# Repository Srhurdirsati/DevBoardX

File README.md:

# DevBoard X
Yo Boizzz , This Is A MACROPAD (not really , it has 20 keys) Named DevBoard X That Includes 20 Keys [Mechanical] with 4x EC11 Rotary Encoders And 1x OLED Diplay...

# FEATURES 
1->> Full Of Functionable Keys { 20 ,MORE THAN ENOUGH }</n>

2->> Rotary Encoders { Cool Scrolllss }</n>

3->> Fully Customizable { Modify The Code For Ur Own Functioning }</n>

# IMAGESSS

# 📋 Bill of Materials (BOM)

| Component | Quantity | Specification | Unit Price | Total Price |
|-----------|----------|---------------|------------|-------------|
| **Microcontroller** | 1 | Raspberry Pi Pico | $4.88 | $4.88 |
| **Rotary Encoders** | 4 | EC11 (Vertical, 20mm shaft) | 0.87 | 3.48 |
| **Keyswitches** | 20 | Outemu Red Cherry MX  | 1.51 | $20 |
| **Diodes** | 20 | 1N4148 (THT) | $0.3 | $2.32 |
| **PCB** | 5 | Custom macropad (5x4 matrix) | $25 with shipping | $25 with shipping |
| **Case & Knobs** | 1 | 3D Printed | Done By Printing Legion | Done By Printing Legion |
| **USB Cable** | 1 | Micro-USB or USB-C | $3.32 | $2.32 |

## JLCPCB

**IDK WHY EVERYTHING IS SO EXPENSIVE IN INDIA**

**Total Estimated Cost**: `$72-75 WITH SHIPPING CHARGES INCLUDED`
**I Tried My best To Decrease The cost As Much As Possible , Would Be Much Cheaper If I Was In US**

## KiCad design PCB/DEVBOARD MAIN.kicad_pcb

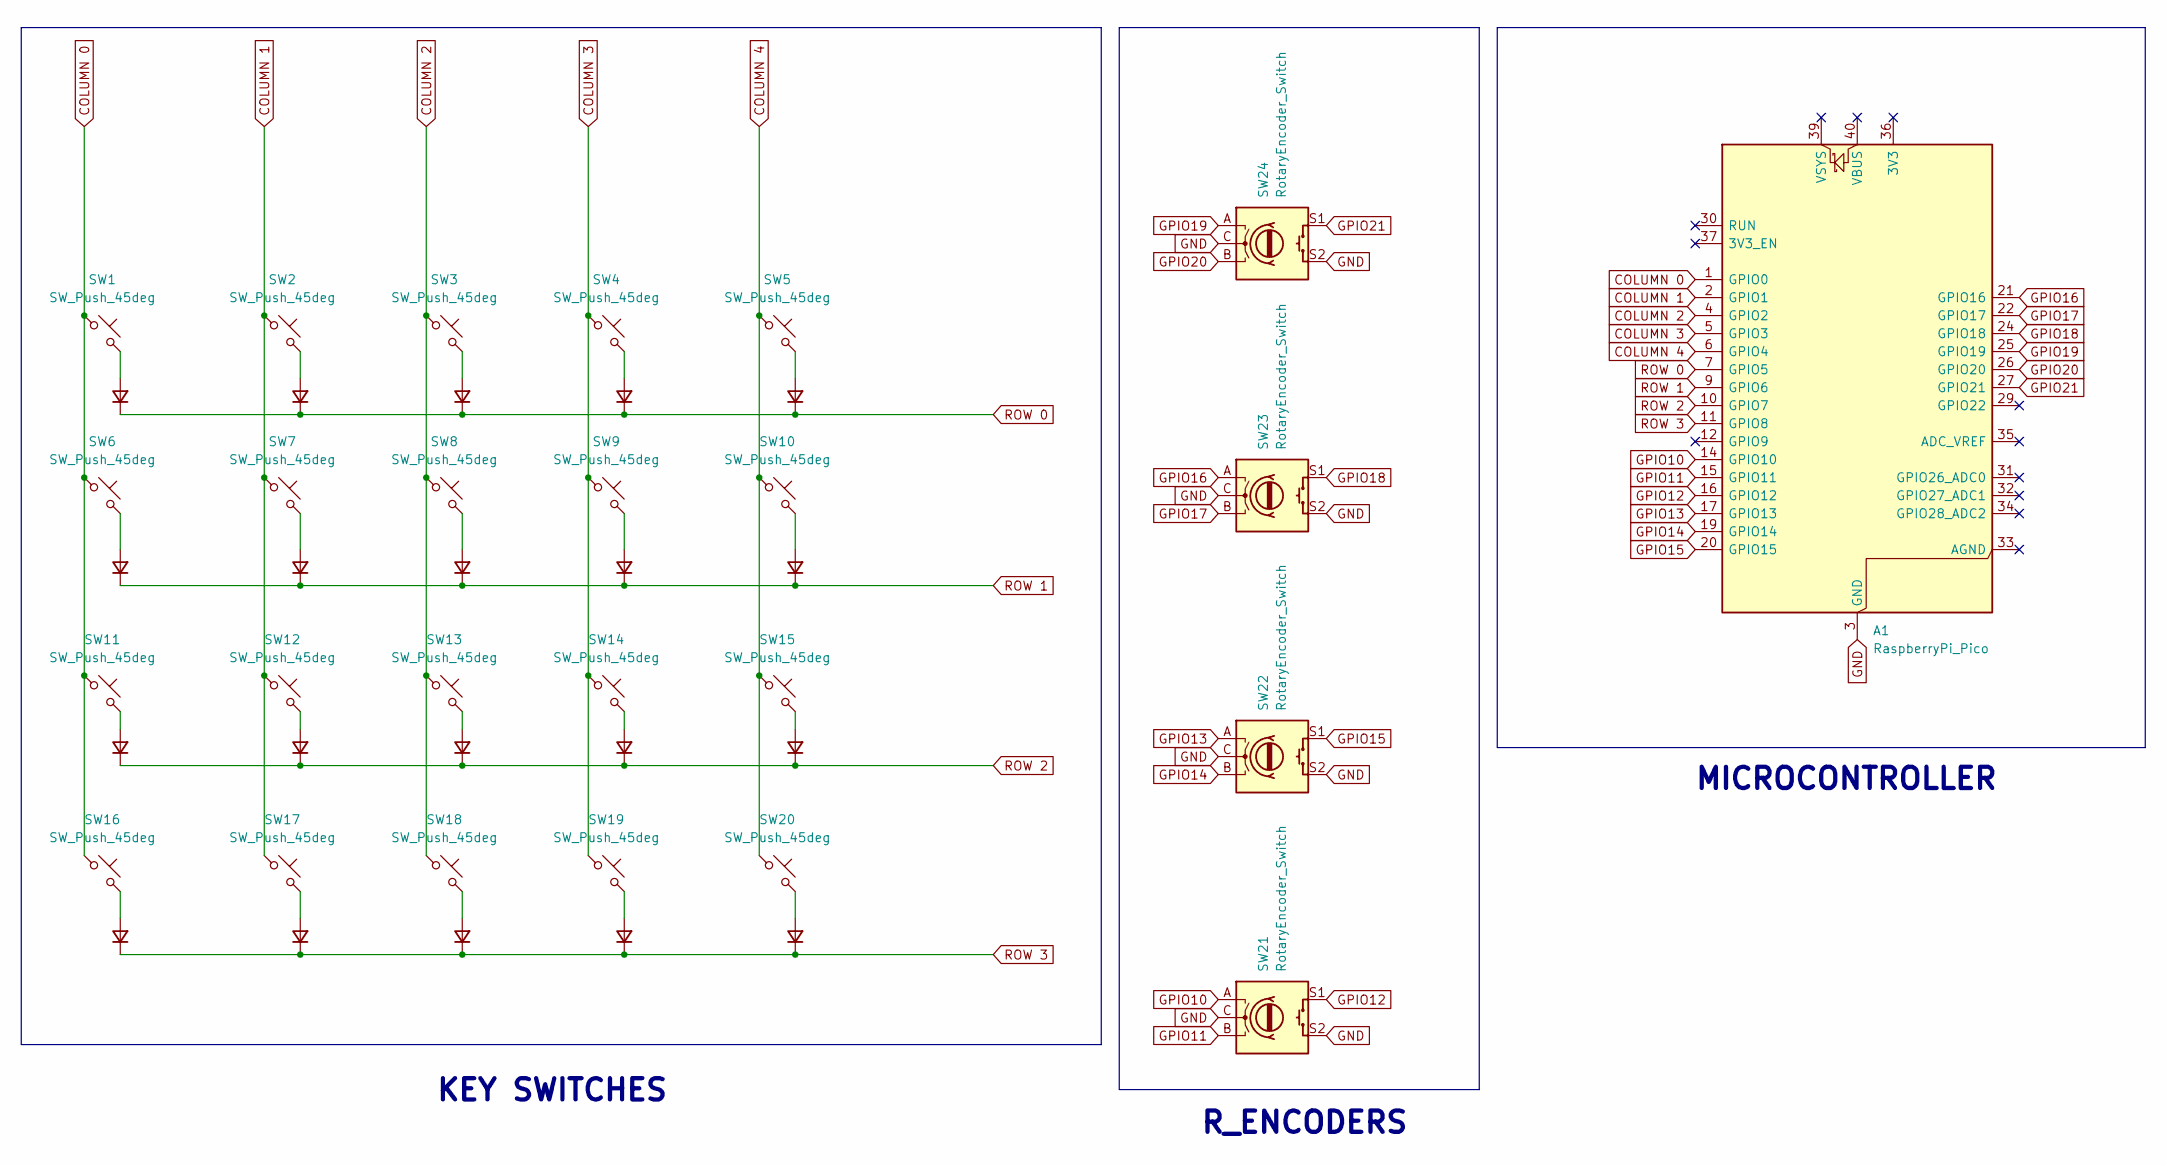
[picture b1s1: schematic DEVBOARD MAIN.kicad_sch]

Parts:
A1: RaspberryPi_Pico; RaspberryPi_Pico_Common_Unspecified
D1, D2, D3, D4, D5, D6, D7, D8, D9, D10, D11, D12, D13, D14, D15, D16, D17, D18, D19: D_Small; D_DO-35_SOD27_P7.62mm_Horizontal
D57: 1N4148; D_DO-35_SOD27_P7.62mm_Horizontal
SW1, SW2, SW3, SW4, SW5, SW6, SW7, SW8, SW9, SW10, SW11, SW12, SW13, SW14, SW15, SW16, SW17, SW18, SW19, SW20: SW_Push_45deg; SW_Cherry_MX_1.00u_PCB
SW21, SW22, SW23, SW24: RotaryEncoder_Switch; RotaryEncoder_Alps_EC11E-Switch_Vertical_H20mm

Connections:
COLUMN 0: A1.1 (GPIO0), SW1.1, SW6.1, SW11.1, SW16.1
COLUMN 1: A1.2 (GPIO1), SW2.1, SW7.1, SW12.1, SW17.1
COLUMN 2: A1.4 (GPIO2), SW3.1, SW8.1, SW13.1, SW18.1
COLUMN 3: A1.5 (GPIO3), SW4.1, SW9.1, SW14.1, SW19.1
COLUMN 4: A1.6 (GPIO4), SW5.1, SW10.1, SW15.1, SW20.1
GND: A1.3 (GND), A1.8 (GND), A1.13 (GND), A1.18 (GND), A1.23 (GND), A1.28 (GND), A1.38 (GND), SW21.C, SW21.S2, SW22.C, SW22.S2, SW23.C, SW23.S2, SW24.C, SW24.S2
GPIO10: A1.14 (GPIO10), SW21.A
GPIO11: A1.15 (GPIO11), SW21.B
GPIO12: A1.16 (GPIO12), SW21.S1
GPIO13: A1.17 (GPIO13), SW22.A
GPIO14: A1.19 (GPIO14), SW22.B
GPIO15: A1.20 (GPIO15), SW22.S1
GPIO16: A1.21 (GPIO16), SW23.A
GPIO17: A1.22 (GPIO17), SW23.B
GPIO18: A1.24 (GPIO18), SW23.S1
GPIO19: A1.25 (GPIO19), SW24.A
GPIO20: A1.26 (GPIO20), SW24.B
GPIO21: A1.27 (GPIO21), SW24.S1
unnamed: D1.2 (A), SW6.2
unnamed: D2.2 (A), SW11.2
unnamed: D3.2 (A), SW16.2
unnamed: D4.2 (A), SW2.2
unnamed: D5.2 (A), SW7.2
unnamed: D6.2 (A), SW12.2
unnamed: D7.2 (A), SW17.2
unnamed: D8.2 (A), SW3.2
unnamed: D9.2 (A), SW8.2
unnamed: D10.2 (A), SW13.2
unnamed: D11.2 (A), SW18.2
unnamed: D12.2 (A), SW4.2
unnamed: D13.2 (A), SW9.2
unnamed: D14.2 (A), SW14.2
unnamed: D15.2 (A), SW19.2
unnamed: D16.2 (A), SW5.2
unnamed: D17.2 (A), SW10.2
unnamed: D18.2 (A), SW15.2
unnamed: D19.2 (A), SW20.2
unnamed: D57.2 (A), SW1.2
ROW 0: A1.7 (GPIO5), D4.1 (K), D8.1 (K), D12.1 (K), D16.1 (K), D57.1 (K)
ROW 1: A1.9 (GPIO6), D1.1 (K), D5.1 (K), D9.1 (K), D13.1 (K), D17.1 (K)
ROW 2: A1.10 (GPIO7), D2.1 (K), D6.1 (K), D10.1 (K), D14.1 (K), D18.1 (K)
ROW 3: A1.11 (GPIO8), D3.1 (K), D7.1 (K), D11.1 (K), D15.1 (K), D19.1 (K)

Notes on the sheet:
MICROCONTROLLER
KEY SWITCHES
R_ENCODERS

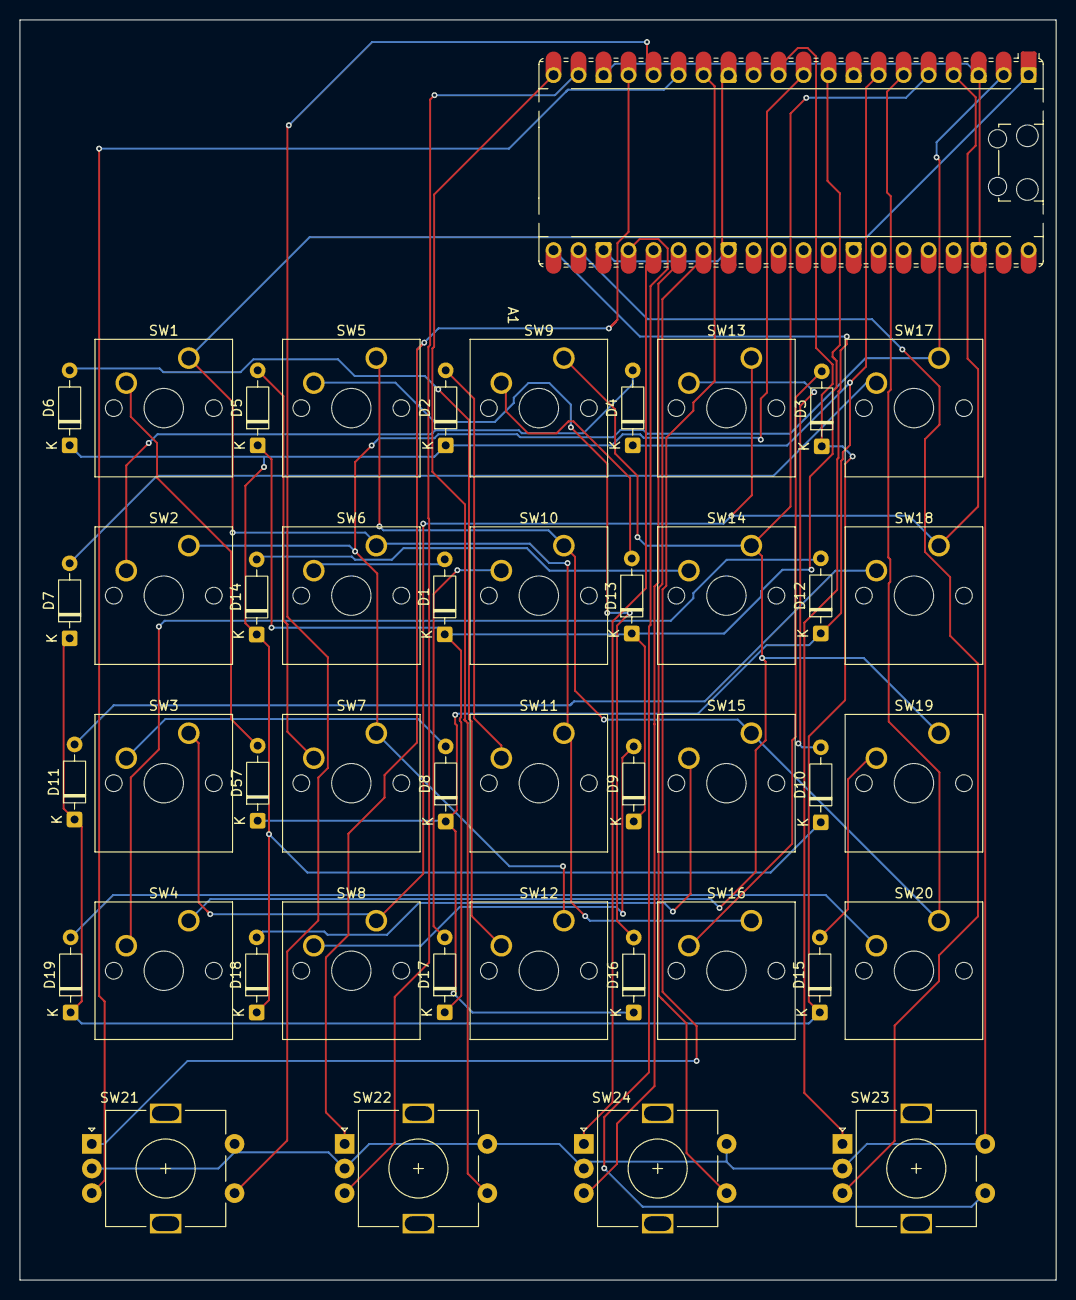
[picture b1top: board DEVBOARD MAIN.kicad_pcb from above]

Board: 2 copper layers, 105.2 x 128.0 mm, 45 parts (0 on the bottom side), 42 nets.

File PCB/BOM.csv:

"Reference","Qty","Value","DNP","Exclude from BOM","Exclude from Board","Footprint","Datasheet"
"A1","1","RaspberryPi_Pico","","","","Module:RaspberryPi_Pico_Common_Unspecified","https://datasheets.raspberrypi.com/pico/pico-datasheet.pdf"
"D1,D2,D3,D4,D5,D6,D7,D8,D9,D10,D11,D12,D13,D14,D15,D16,D17,D18,D19","19","D_Small","","","","Diode_THT:D_DO-35_SOD27_P7.62mm_Horizontal","~"
"D57","1","1N4148","","","","Diode_THT:D_DO-35_SOD27_P7.62mm_Horizontal","~"
"SW1,SW2,SW3,SW4,SW5,SW6,SW7,SW8,SW9,SW10,SW11,SW12,SW13,SW14,SW15,SW16,SW17,SW18,SW19,SW20","20","SW_Push_45deg","","","","Button_Switch_Keyboard:SW_Cherry_MX_1.00u_PCB","~"
"SW21,SW22,SW23,SW24","4","RotaryEncoder_Switch","","","","Rotary_Encoder:RotaryEncoder_Alps_EC11E-Switch_Vertical_H20mm","~"

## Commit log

2025-07-20 Create tmp
